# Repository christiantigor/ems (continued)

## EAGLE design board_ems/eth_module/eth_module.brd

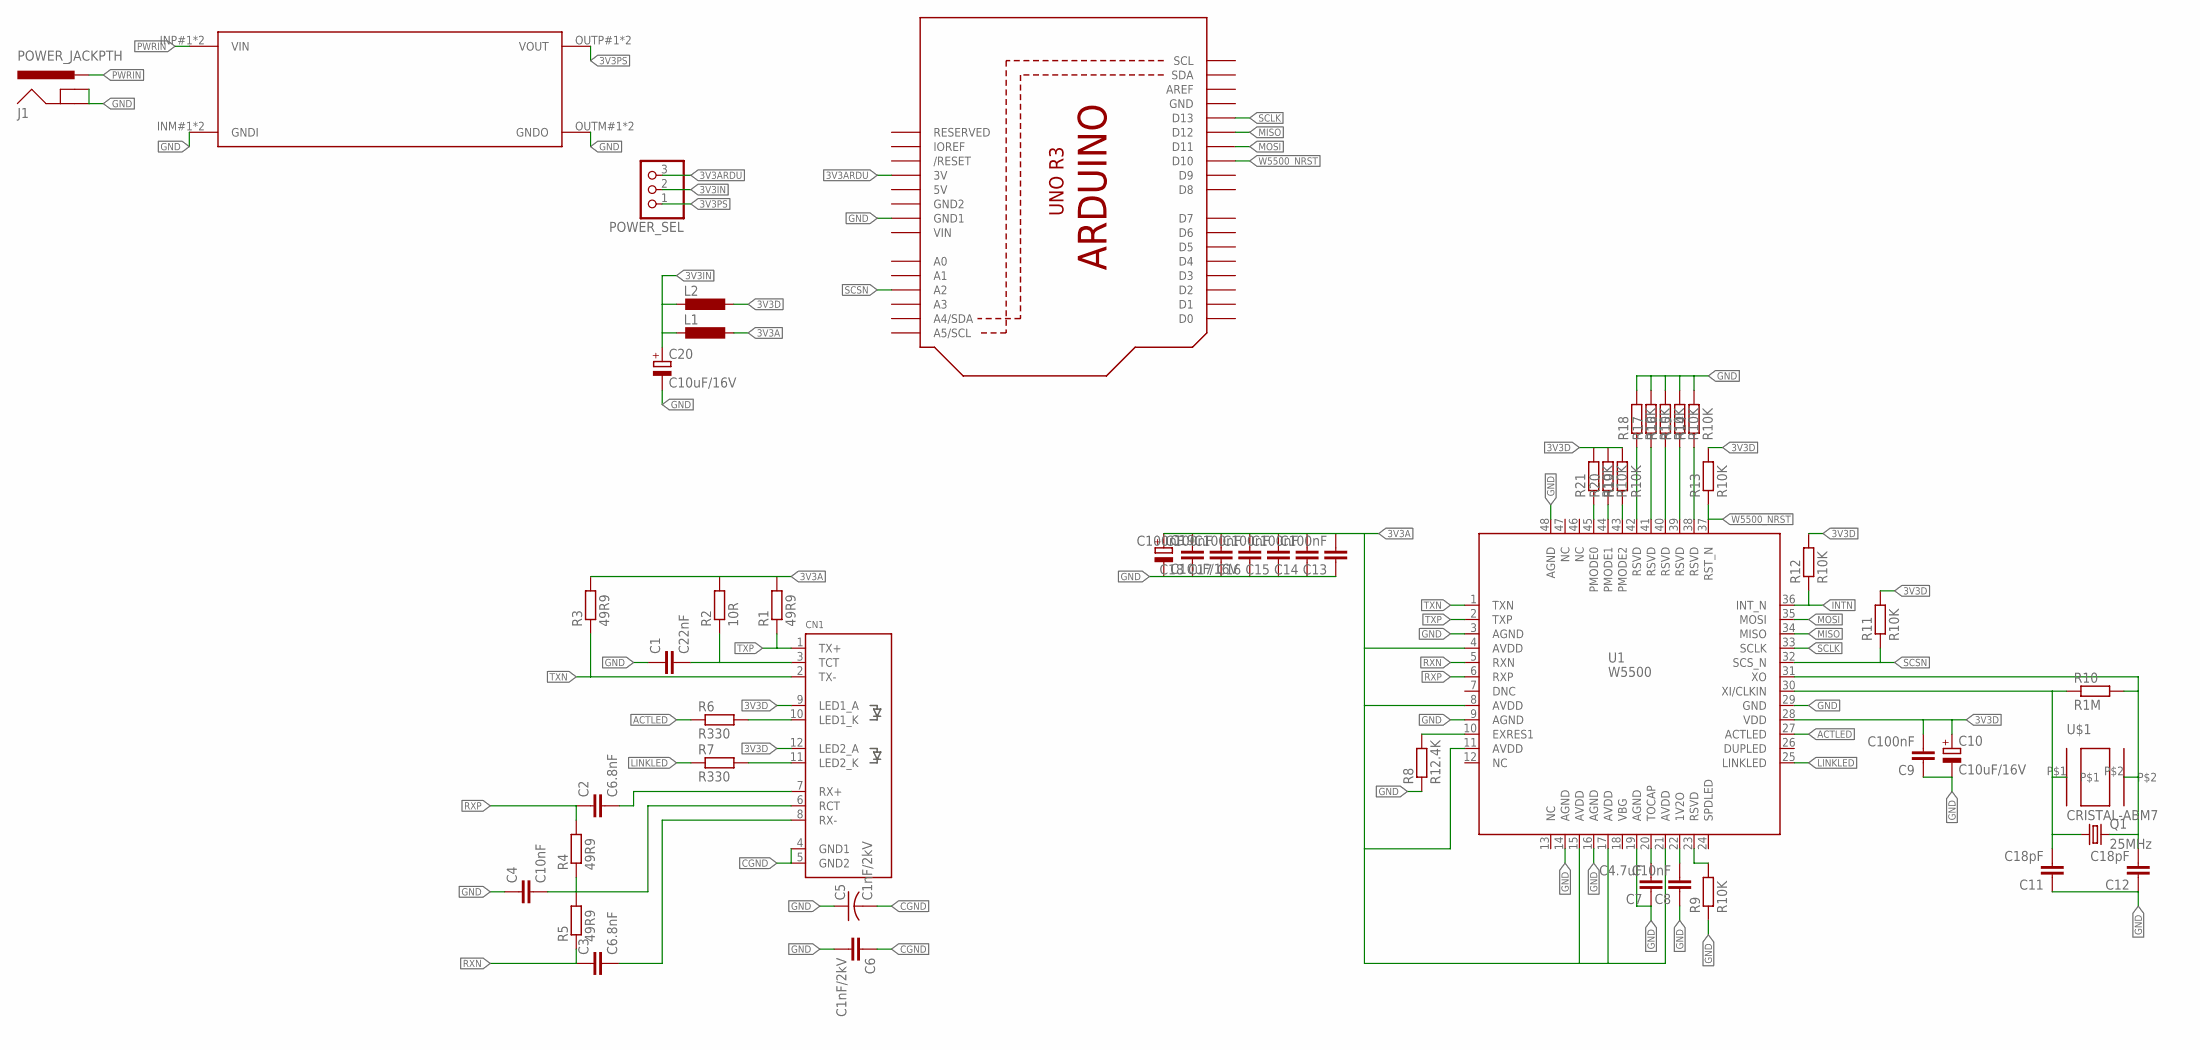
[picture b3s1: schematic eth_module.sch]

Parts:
C1: C22nF; C0603
C2, C3: C6.8nF; C0603
C4, C8: C10nF; C0603
C5: C1nF/2kV; C025-025X050
C6: C1nF/2kV; C0603
C7: C4.7uF; C0603
C9, C13, C14, C15, C16, C17, C18: C100nF; C0603
C10, C19, C20: C10uF/16V; 153CLV-0605
C11, C12: C18pF; C0603
CN1: RJ45J0026D21BNL; RJ45_PULSEJACK
J1: POWER_JACKPTH; POWER_JACK_PTH
L1, L2: L-EUL2012C; L2012C
POWER_SEL: PINHD-1X3; 1X03
Q1: 25MHz; HC49/S
R1, R3, R4, R5: 49R9; R0603
R2: 10R; R0603
R6, R7: R330; R0603
R8: R12.4K; R0805
R9, R11, R12, R13, R14, R15, R16, R17, R18, R19, R20, R21: R10K; R0603
R10: R1M; R0603
U1: W5500
U2: ARDUINOR3-DIMENSION; ARDUINOR3
U$1: CRISTAL-ABM7
U$2: DCDCMODULE_SMALL; DCDCMODULE-SMALL

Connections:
3V3A: C13.2, C14.2, C15.2, C16.2, C17.2, C18.2, C19.+, L1.1, R1.2, R2.2, R3.2, U1.4 (AVDD), U1.8 (AVDD), U1.11 (AVDD), U1.15 (AVDD), U1.17 (AVDD), U1.21 (AVDD)
3V3ARDU: POWER_SEL.3, U2.3V
3V3D: C9.2, C10.+, CN1.9 (LED1_A), CN1.12 (LED2_A), L2.1, R11.2, R12.2, R13.2, R19.2, R20.2, R21.2, U1.28 (VDD)
3V3IN: C20.+, L1.2, L2.2, POWER_SEL.2
3V3PS: POWER_SEL.1, U$2.OUTP#1 (VOUT), U$2.OUTP#2 (VOUT)
5VPS: U2.5V
ACTLED: R6.1, U1.27 (ACTLED)
CGND: C5.2, C6.1, CN1.4 (GND1), CN1.5 (GND2)
GND: C1.1, C4.1, C5.1, C6.2, C7.1, C8.1, C9.1, C10.-, C11.1, C12.1, C13.1, C14.1, C15.1, C16.1, C17.1, C18.1, C19.-, C20.-, J1.GND, J1.GNDBREAK, R8.1, R9.1, R14.2, R15.2, R16.2, R17.2, R18.2, U1.3 (AGND), U1.9 (AGND), U1.14 (AGND), U1.16 (AGND), U1.19 (AGND), U1.29 (GND), U1.48 (AGND), U2.GND, U2.GND1, U$2.INM#1 (GNDI), U$2.INM#2 (GNDI), U$2.OUTM#1 (GNDO), U$2.OUTM#2 (GNDO)
GND2: U2.GND2
INTN: R12.1, U1.36 (INT_N)
LINKLED: R7.1, U1.25 (LINKLED)
MISO: U1.34 (MISO), U2.D12
MOSI: U1.35 (MOSI), U2.D11
unnamed: CN1.10 (LED1_K), R6.2
unnamed: C1.2, CN1.3 (TCT), R2.1
unnamed: CN1.11 (LED2_K), R7.2
unnamed: C2.2, CN1.7 (RX+)
unnamed: C7.2, U1.20 (TOCAP)
unnamed: C4.2, CN1.6 (RCT), R4.1, R5.2
unnamed: R9.2, U1.23 (RSVD)
unnamed: C3.2, CN1.8 (RX-)
unnamed: R8.2, U1.10 (EXRES1)
unnamed: C11.2, Q1.1, R10.1, U1.30 (XI/CLKIN), U$1.P$1
unnamed: C8.2, U1.22 (1V2O)
unnamed: C12.2, Q1.2, R10.2, U1.31 (XO), U$1.P$2
unnamed: R14.1, U1.38 (RSVD)
unnamed: R15.1, U1.39 (RSVD)
unnamed: R16.1, U1.40 (RSVD)
unnamed: R17.1, U1.41 (RSVD)
unnamed: R18.1, U1.42 (RSVD)
unnamed: R21.1, U1.45 (PMODE0)
unnamed: R20.1, U1.44 (PMODE1)
unnamed: R19.1, U1.43 (PMODE2)
PWRIN: J1.PWR, U$2.INP#1 (VIN), U$2.INP#2 (VIN)
RXN: C3.1, R5.1, U1.5 (RXN)
RXP: C2.1, R4.2, U1.6 (RXP)
SCLK: U1.33 (SCLK), U2.D13
SCSN: R11.1, U1.32 (SCS_N), U2.A2
TXN: CN1.2 (TX-), R3.1, U1.1 (TXN)
TXP: CN1.1 (TX+), R1.1, U1.2 (TXP)
VIN: U2.VIN
W5500_NRST: R13.1, U1.37 (RST_N), U2.D10

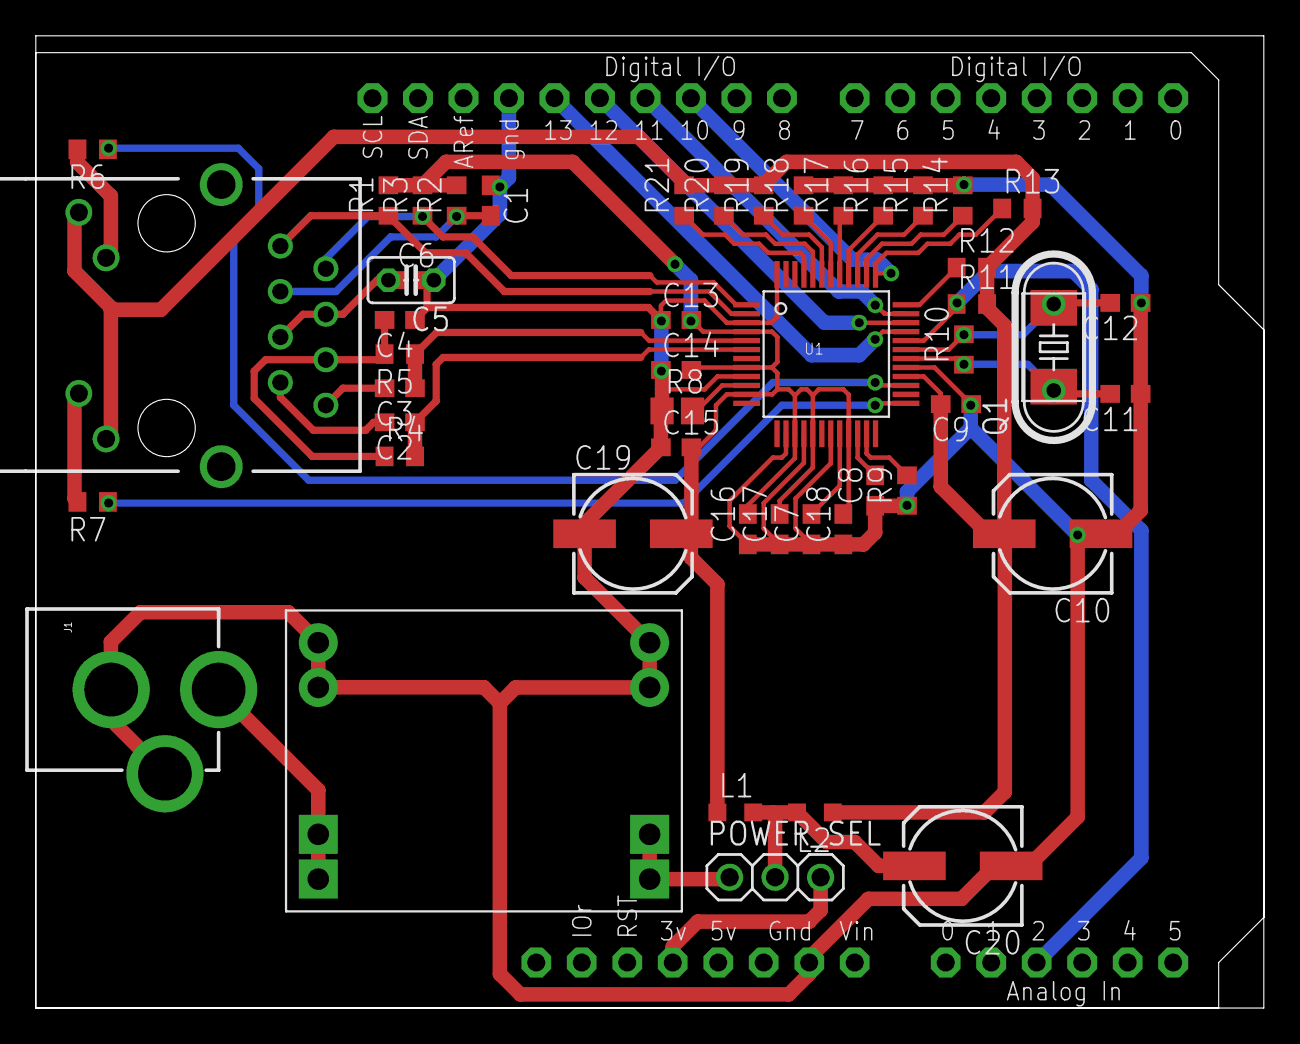
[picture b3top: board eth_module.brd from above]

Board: 2 copper layers, 68.6 x 54.3 mm, 51 parts (0 on the bottom side), 40 nets.

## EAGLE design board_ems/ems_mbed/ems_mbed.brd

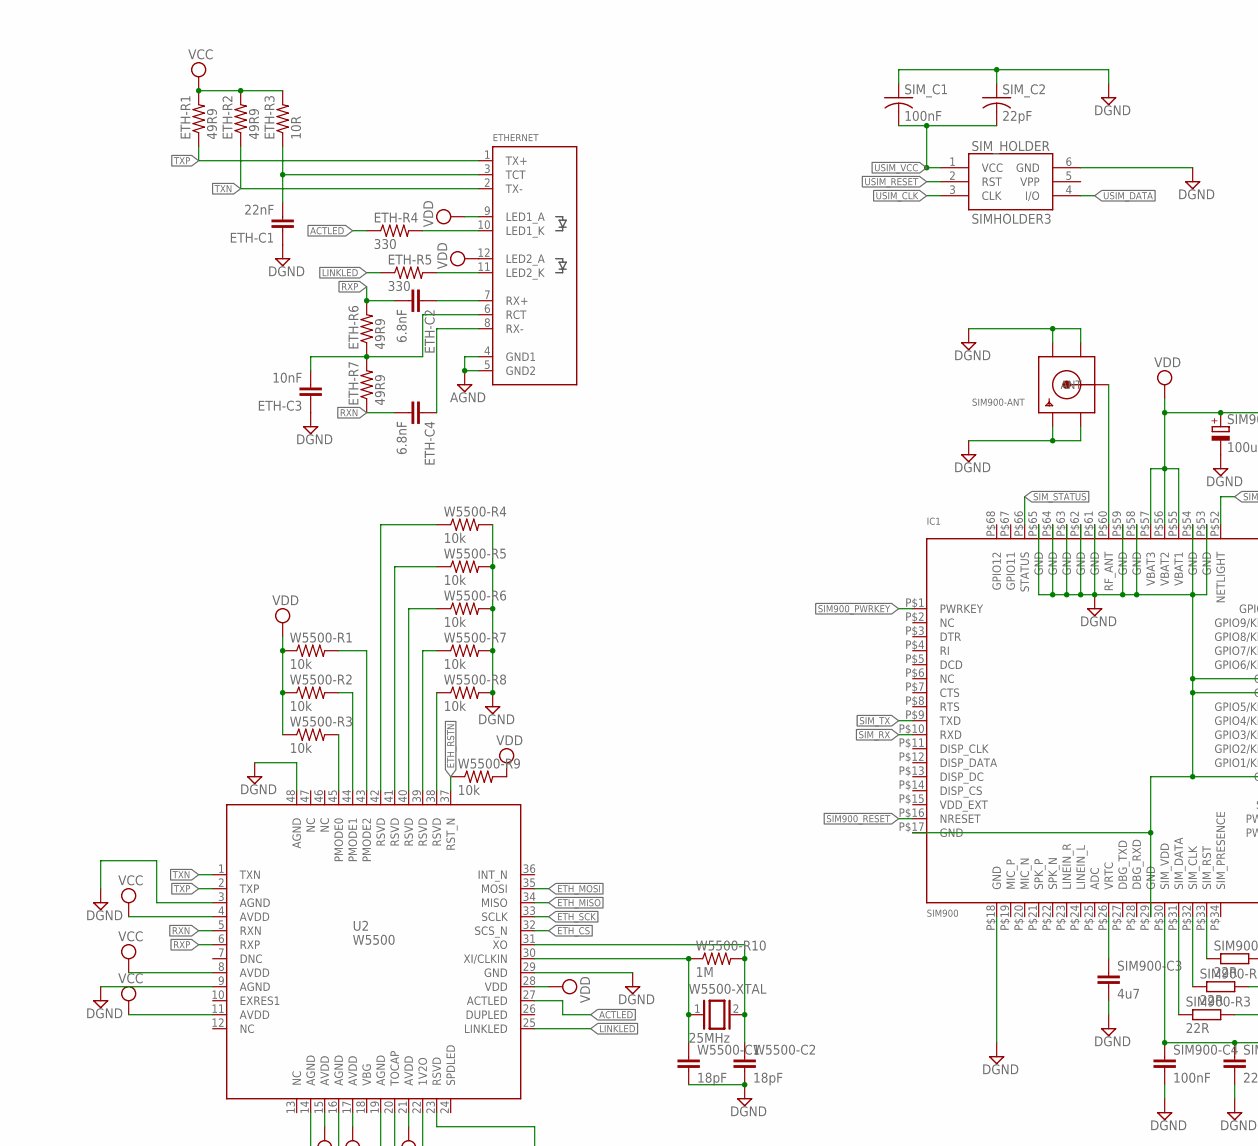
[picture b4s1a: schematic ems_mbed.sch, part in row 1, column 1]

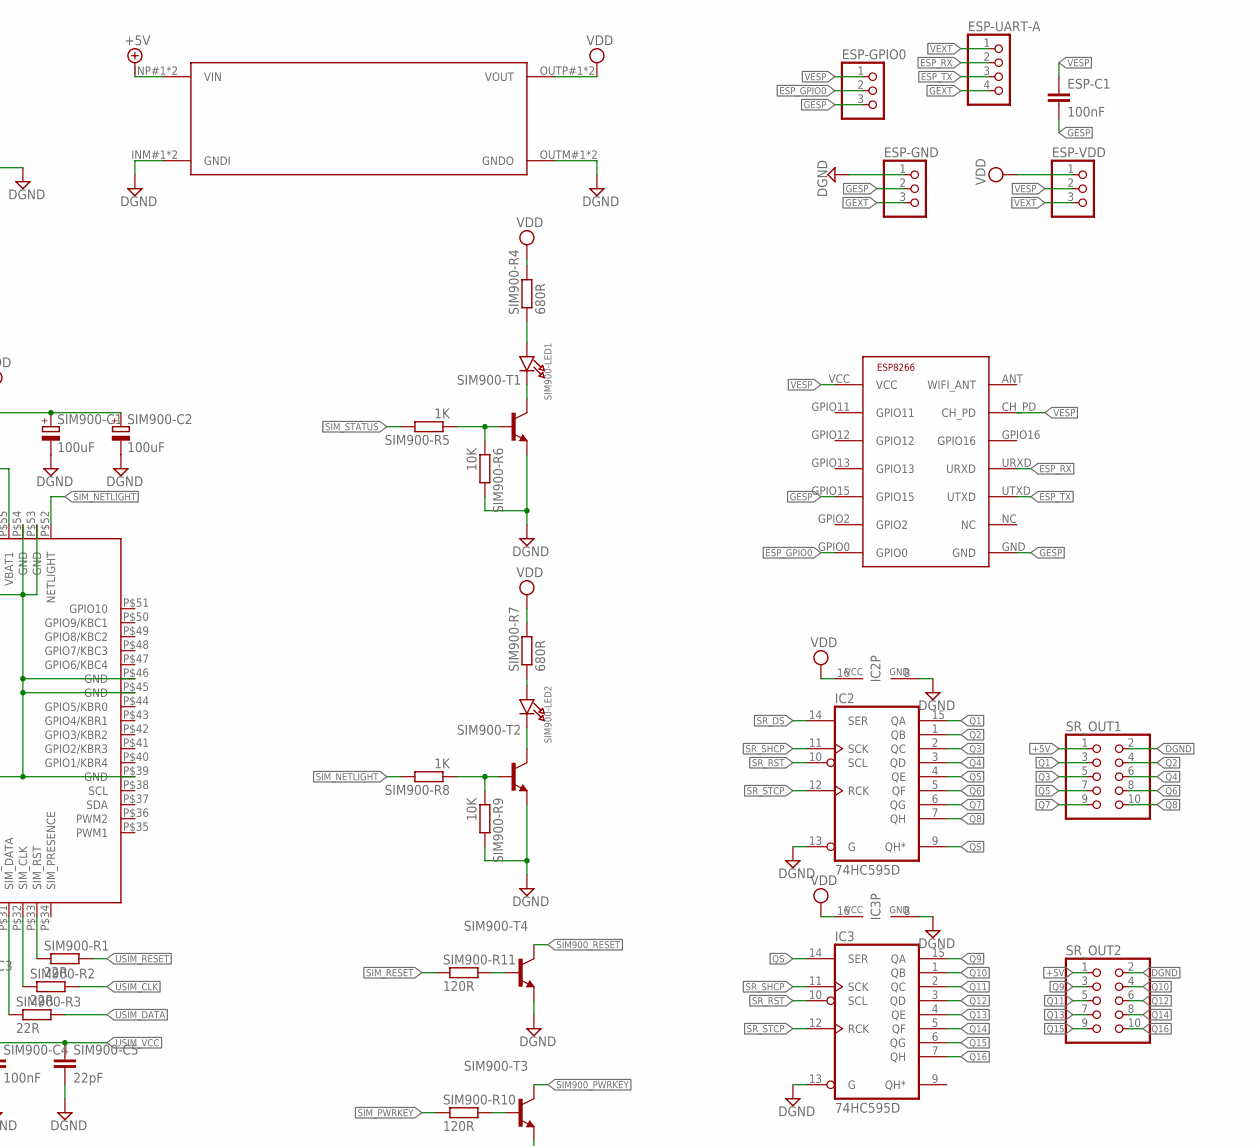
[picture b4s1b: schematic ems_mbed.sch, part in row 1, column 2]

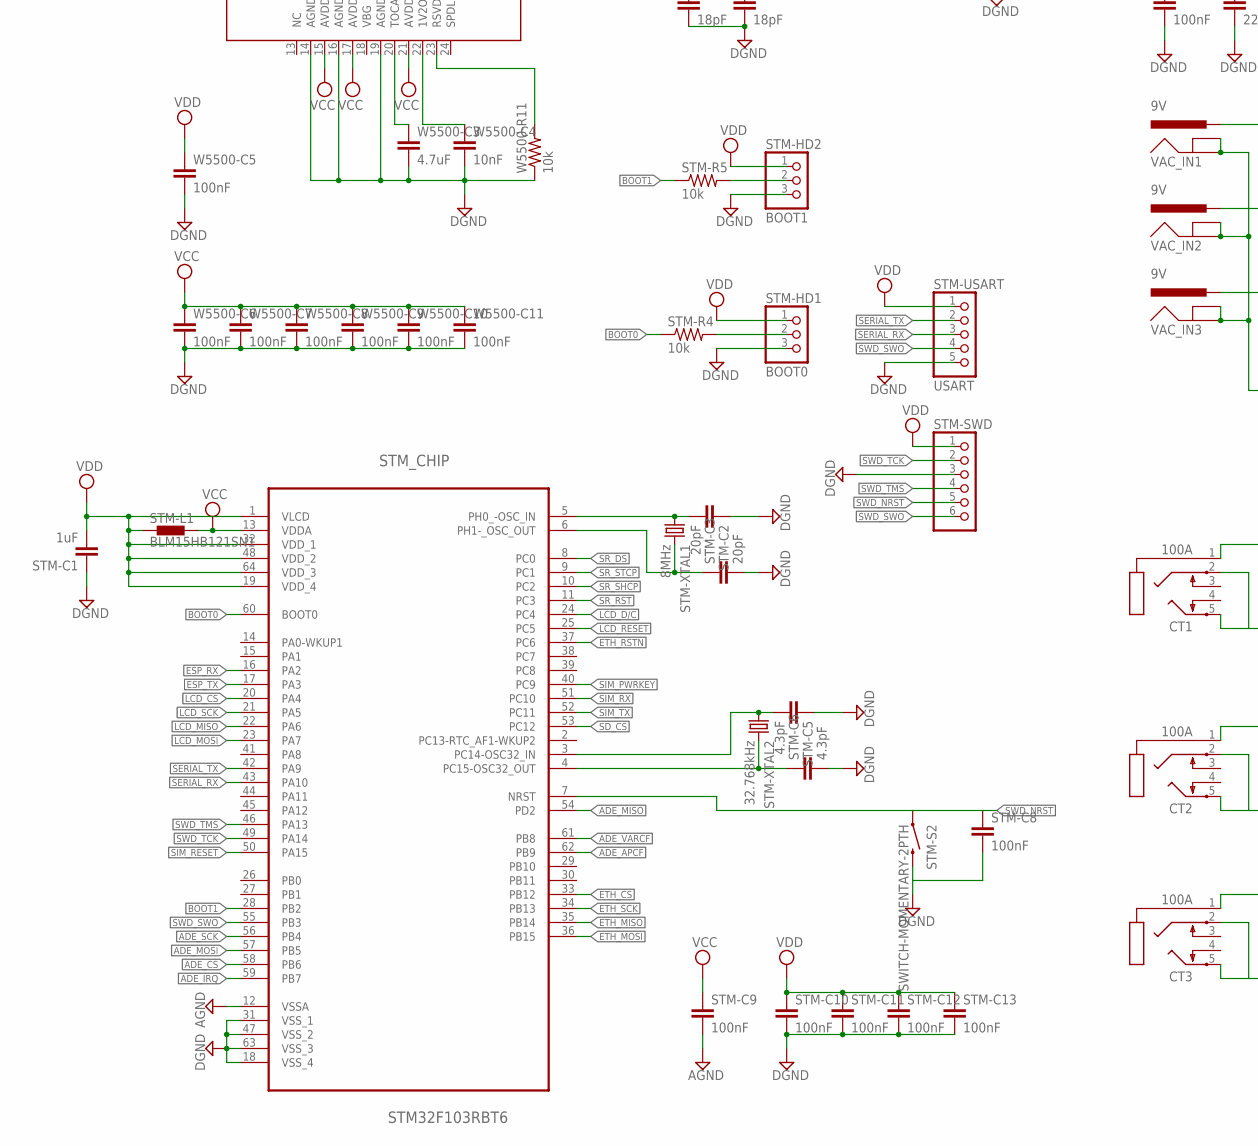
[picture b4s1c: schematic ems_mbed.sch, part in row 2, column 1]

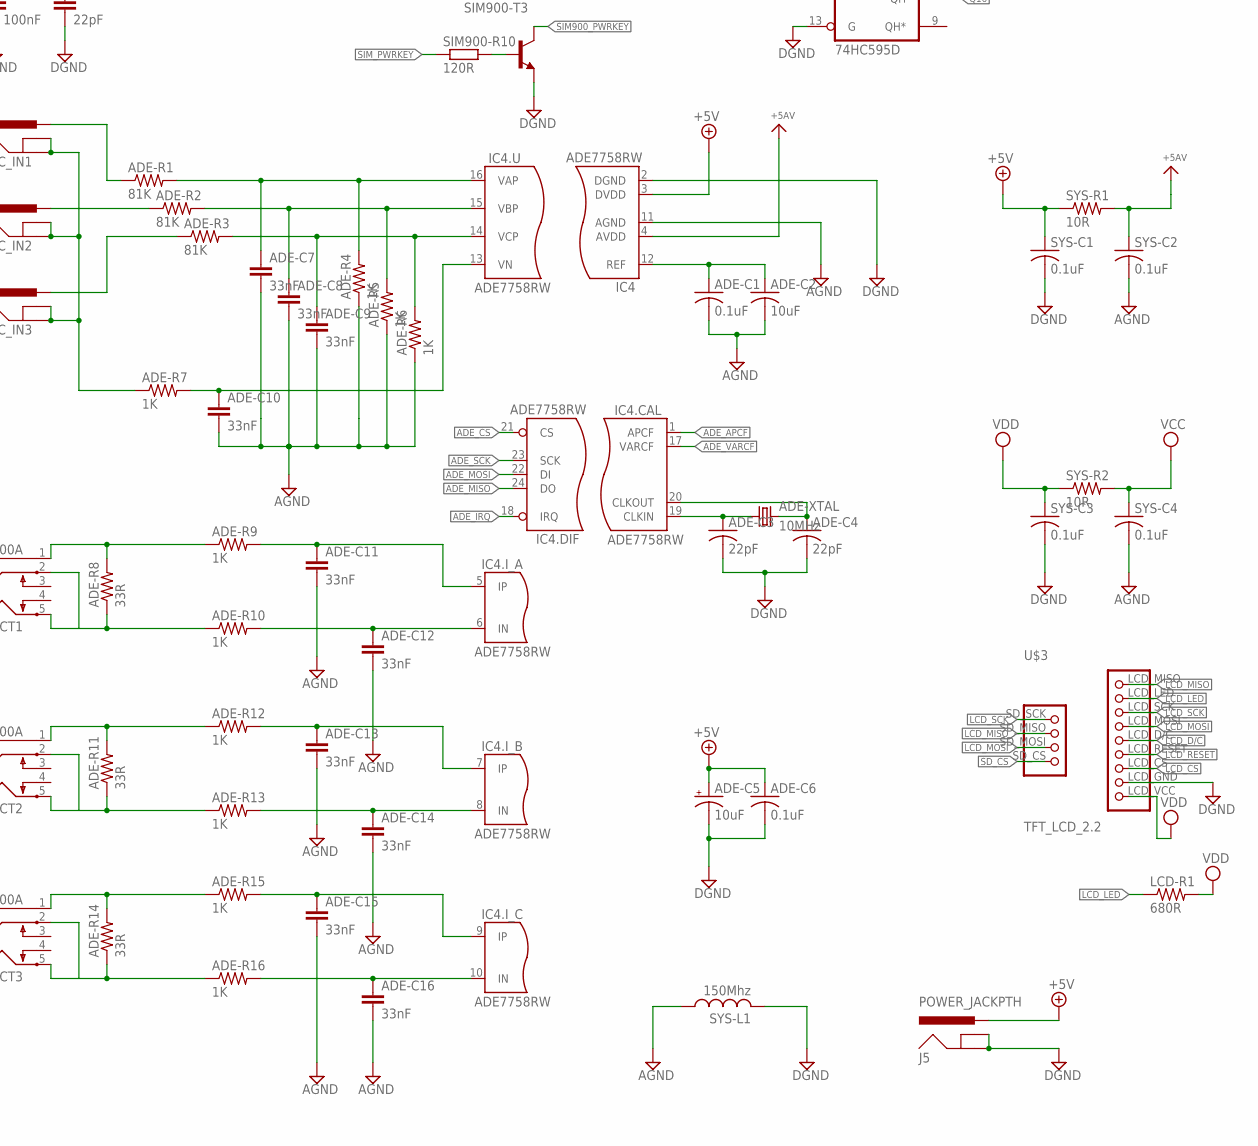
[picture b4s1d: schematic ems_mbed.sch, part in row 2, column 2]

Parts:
ADE-C1, ADE-C6: 0.1uF; C0603@1
ADE-C2: 10uF; C0805K
ADE-C3: 22pF; C0603@1
ADE-C4: 22pF; C0603
ADE-C5: 10uF; 153CLV-0605
ADE-C7, ADE-C8, ADE-C9, ADE-C10, ADE-C11, ADE-C12, ADE-C13, ADE-C14, ADE-C15, ADE-C16: 33nF; 0603-CAP
ADE-R1, ADE-R2, ADE-R3: 81K; 0603-RES
ADE-R4, ADE-R5, ADE-R6, ADE-R7, ADE-R9, ADE-R10, ADE-R12, ADE-R13, ADE-R15, ADE-R16: 1K; 0603-RES
ADE-R8, ADE-R11, ADE-R14: 33R; 0603-RES
ADE-XTAL: 10MHz; HC49US
CT1, CT2, CT3: 100A; STX3100
DCDC-3.5V: DCDCMODULE_SMALL; DCDCMODULE-SMALL
ESP8266: ESP-07
ESP-C1: 100nF; C0603@1
ESP-GND: PINHD-1X3; 1X03
ESP-GPIO0: PINHD-1X3; 1X03
ESP-UART-A: PINHD-1X4; 1X04
ESP-VDD: PINHD-1X3; 1X03
ETH-C1: 22nF; C0603@1
ETH-C2, ETH-C4: 6.8nF; C0603@1
ETH-C3: 10nF; C0603@1
ETH-R1, ETH-R2, ETH-R6, ETH-R7: 49R9; R0603
ETH-R3: 10R; R0603
ETH-R4, ETH-R5: 330; R0603
ETHERNET: RJ45J0026D21BNL; RJ45_PULSEJACK
IC1: SIM900; SIM900_SMT
IC2, IC3: 74HC595D; SO16
IC4: ADE7758RW; SOIC24
J5: POWER_JACKPTH; POWER_JACK_PTH
LCD-R1: 680R; 0603-RES
SIM900-ANT: SMACONNECTOR; SMA90_DIP
SIM900-C1, SIM900-C2: 100uF; 153CLV-0605
SIM900-C3: 4u7; C0603@1
SIM900-C4: 100nF; C0603@1
SIM900-C5: 22pF; C0603@1
SIM900-LED1, SIM900-LED2: LED0805_NOOUTLINE; CHIPLED_0805_NOOUTLINE
SIM900-R1, SIM900-R2, SIM900-R3: 22R; R0603
SIM900-R4, SIM900-R7: 680R; R0603
SIM900-R5, SIM900-R8: 1K; R0603
SIM900-R6, SIM900-R9: 10K; R0603
SIM900-R10, SIM900-R11: 120R; R0603
SIM900-T1, SIM900-T2, SIM900-T3, SIM900-T4: MMBT2222ALT1-NPN-SOT23-BEC; SOT23-BEC
SIM_C1: 100nF; C0603K
SIM_C2: 22pF; C0603K
SIM_HOLDER: SIMHOLDER3
SR_OUT1, SR_OUT2: PINHD-2X5/90; 2X05/90
STM-C1: 1uF; C0603@1
STM-C2, STM-C3: 20pF; C0603@1
STM-C5, STM-C6: 4.3pF; C0603@1
STM-C8, STM-C9, STM-C10, STM-C11, STM-C12, STM-C13: 100nF; C0603@1
STM-HD1: BOOT0; 1X03
STM-HD2: BOOT1; 1X03
STM-L1: BLM15HB121SN1; 0402
STM-R4, STM-R5: 10k; R0603
STM-S2: SWITCH-MOMENTARY-2PTH; TACTILE-PTH
STM-SWD: PINHD-1X6; 1X06
STM-USART: USART; PINHD5
STM-XTAL1: 8MHz; TC26H
STM-XTAL2: 32.768kHz; TC26H
STM_CHIP: STM32F103RBT6; QFP50P1200X1200X160-64N
SYS-C1, SYS-C2, SYS-C3, SYS-C4: 0.1uF; C0603@1
SYS-L1: 150Mhz; POWER-CHOKE_WE-TPC
SYS-R1, SYS-R2: 10R; 0603-RES
U2: W5500
U$3: TFT_LCD_2.2
VAC_IN1, VAC_IN2, VAC_IN3: 9V; POWER_JACK_PTH
W5500-C1, W5500-C2: 18pF; C0603@1
W5500-C3: 4.7uF; C0603@1
W5500-C4: 10nF; C0603@1
W5500-C5, W5500-C6, W5500-C7, W5500-C8, W5500-C9, W5500-C10, W5500-C11: 100nF; C0603@1
W5500-R1, W5500-R2, W5500-R3, W5500-R4, W5500-R5, W5500-R6, W5500-R7, W5500-R8, W5500-R9, W5500-R11: 10k; R0603
W5500-R10: 1M; R0603
W5500-XTAL: 25MHz; QS

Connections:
+5V: ADE-C5.+, ADE-C6.1, DCDC-3.5V.INP#1 (VIN), DCDC-3.5V.INP#2 (VIN), IC4.3 (DVDD), J5.PWR, SR_OUT1.1, SR_OUT2.1, SYS-C1.1, SYS-R1.1
ACTLED: ETH-R4.1, U2.27 (ACTLED)
ADE_APCF: IC4.1 (APCF), STM_CHIP.62 (PB9)
ADE_CS: IC4.21 (CS), STM_CHIP.58 (PB6)
ADE_IRQ: IC4.18 (IRQ), STM_CHIP.59 (PB7)
ADE_MISO: IC4.24 (DO), STM_CHIP.54 (PD2)
ADE_MOSI: IC4.22 (DI), STM_CHIP.57 (PB5)
ADE_SCK: IC4.23 (SCK), STM_CHIP.56 (PB4)
ADE_VARCF: IC4.17 (VARCF), STM_CHIP.61 (PB8)
AGND: ADE-C1.2, ADE-C2.2, ADE-C7.2, ADE-C8.2, ADE-C9.2, ADE-C10.2, ADE-C11.2, ADE-C12.2, ADE-C13.2, ADE-C14.2, ADE-C15.2, ADE-C16.2, ADE-R4.1, ADE-R5.1, ADE-R6.1, ETHERNET.4 (GND1), ETHERNET.5 (GND2), IC4.11 (AGND), STM-C9.2, STM_CHIP.12 (VSSA), SYS-C2.2, SYS-C4.2, SYS-L1.1
AVDD: IC4.4 (AVDD), SYS-C2.1, SYS-R1.2
BOOT0: STM-R4.1, STM_CHIP.60 (BOOT0)
BOOT1: STM-R5.1, STM_CHIP.28 (PB2)
DGND: ADE-C3.2, ADE-C4.2, ADE-C5.-, ADE-C6.2, DCDC-3.5V.INM#1 (GNDI), DCDC-3.5V.INM#2 (GNDI), DCDC-3.5V.OUTM#1 (GNDO), DCDC-3.5V.OUTM#2 (GNDO), ESP-GND.1, ETH-C1.1, ETH-C3.1, IC1.P$17 (GND), IC1.P$18 (GND), IC1.P$29 (GND), IC1.P$39 (GND), IC1.P$45 (GND), IC1.P$46 (GND), IC1.P$53 (GND), IC1.P$54 (GND), IC1.P$58 (GND), IC1.P$59 (GND), IC1.P$61 (GND), IC1.P$62 (GND), IC1.P$63 (GND), IC1.P$64 (GND), IC1.P$65 (GND), IC2.8 (GND), IC2.13 (G), IC3.8 (GND), IC3.13 (G), IC4.2 (DGND), J5.GND, J5.GNDBREAK, SIM900-ANT.GND1, SIM900-ANT.GND2, SIM900-ANT.GND3, SIM900-ANT.GND4, SIM900-C1.-, SIM900-C2.-, SIM900-C3.2, SIM900-C4.2, SIM900-C5.2, SIM900-R6.2, SIM900-R9.2, SIM900-T1.E, SIM900-T2.E, SIM900-T3.E, SIM900-T4.E, SIM_C1.1, SIM_C2.1, SIM_HOLDER.6 (GND), SR_OUT1.2, SR_OUT2.2, STM-C1.1, STM-C2.1, STM-C3.2, STM-C5.1, STM-C6.2, STM-C8.2, STM-C10.2, STM-C11.2, STM-C12.2, STM-C13.2, STM-HD1.3, STM-HD2.3, STM-S2.3 (2), STM-SWD.3, STM-USART.5, STM_CHIP.18 (VSS_4), STM_CHIP.31 (VSS_1), STM_CHIP.47 (VSS_2), STM_CHIP.63 (VSS_3), SYS-C1.2, SYS-C3.2, SYS-L1.2, U2.3 (AGND), U2.9 (AGND), U2.14 (AGND), U2.16 (AGND), U2.19 (AGND), U2.29 (GND), U2.48 (AGND), U$3.LCD_GND, W5500-C1.2, W5500-C2.2, W5500-C3.2, W5500-C4.2, W5500-C5.2, W5500-C6.2, W5500-C7.2, W5500-C8.2, W5500-C9.2, W5500-C10.2, W5500-C11.2, W5500-R4.2, W5500-R5.2, W5500-R6.2, W5500-R7.2, W5500-R8.2, W5500-R11.1
ESP_GPIO0: ESP8266.GPIO0, ESP-GPIO0.2
ESP_RX: ESP8266.URXD, ESP-UART-A.2, STM_CHIP.16 (PA2)
ESP_TX: ESP8266.UTXD, ESP-UART-A.3, STM_CHIP.17 (PA3)
ETH_CS: STM_CHIP.33 (PB12), U2.32 (SCS_N)
ETH_MISO: STM_CHIP.35 (PB14), U2.34 (MISO)
ETH_MOSI: STM_CHIP.36 (PB15), U2.35 (MOSI)
ETH_RSTN: STM_CHIP.37 (PC6), U2.37 (RST_N), W5500-R9.1
ETH_SCK: STM_CHIP.34 (PB13), U2.33 (SCLK)
GESP: ESP8266.GND, ESP8266.GPIO15, ESP-C1.2, ESP-GND.2, ESP-GPIO0.3
GEXT: ESP-GND.3, ESP-UART-A.4
GPIO11: IC1.P$67 (GPIO11)
GPIO12: IC1.P$68 (GPIO12)
IBN: ADE-R11.1, ADE-R13.1, CT2.2, CT2.5
ICN: ADE-R14.1, ADE-R16.1, CT3.2, CT3.5
LCD_CS: STM_CHIP.20 (PA4), U$3.LCD_CS
LCD_D/C: STM_CHIP.24 (PC4), U$3.LCD_D/C
LCD_LED: LCD-R1.1, U$3.LCD_LED
LCD_MISO: STM_CHIP.22 (PA6), U$3.LCD_MISO, U$3.SD_MISO
LCD_MOSI: STM_CHIP.23 (PA7), U$3.LCD_MOSI, U$3.SD_MOSI
LCD_RESET: STM_CHIP.25 (PC5), U$3.LCD_RESET
LCD_SCK: STM_CHIP.21 (PA5), U$3.LCD_SCK, U$3.SD_SCK
LINKLED: ETH-R5.1, U2.25 (LINKLED)
unnamed: STM-C5.2, STM-XTAL2.1, STM_CHIP.3 (PC14-OSC32_IN)
unnamed: STM-C6.1, STM-XTAL2.2, STM_CHIP.4 (PC15-OSC32_OUT)
unnamed: IC1.P$31 (SIM_DATA), SIM900-R3.1
unnamed: STM-HD1.2, STM-R4.2
unnamed: STM-C2.2, STM-XTAL1.1, STM_CHIP.5 (PH0_-OSC_IN)
unnamed: STM-C3.1, STM-XTAL1.2, STM_CHIP.6 (PH1-_OSC_OUT)
unnamed: IC1.P$32 (SIM_CLK), SIM900-R2.1
unnamed: ADE-C9.1, ADE-R3.2, ADE-R6.2, IC4.14 (VCP)
unnamed: ETH-R4.2, ETHERNET.10 (LED1_K)
unnamed: ETH-R5.2, ETHERNET.11 (LED2_K)
unnamed: IC1.P$33 (SIM_RST), SIM900-R1.1
unnamed: IC1.P$26 (VRTC), SIM900-C3.1
unnamed: IC1.P$60 (RF_ANT), SIM900-ANT.ANTENNA (ANT)
unnamed: SIM900-LED1.A, SIM900-R4.1
unnamed: SIM900-LED1.C, SIM900-T1.C
unnamed: SIM900-R5.1, SIM900-R6.1, SIM900-T1.B
unnamed: SIM900-LED2.A, SIM900-R7.1
unnamed: SIM900-LED2.C, SIM900-T2.C
unnamed: SIM900-R8.1, SIM900-R9.1, SIM900-T2.B
unnamed: ETH-C2.1, ETHERNET.7 (RX+)
unnamed: ETH-C1.2, ETH-R3.1, ETHERNET.3 (TCT)
unnamed: ADE-C15.1, ADE-R15.2, IC4.9 (IP)
unnamed: ADE-R11.2, ADE-R12.1, CT2.1
unnamed: ETH-C4.1, ETHERNET.8 (RX-)
unnamed: ADE-C11.1, ADE-R9.2, IC4.5 (IP)
unnamed: ADE-C12.1, ADE-R10.2, IC4.6 (IN)
unnamed: ETH-C3.2, ETH-R6.1, ETH-R7.2, ETHERNET.6 (RCT)
unnamed: ADE-C14.1, ADE-R13.2, IC4.8 (IN)
unnamed: ADE-C13.1, ADE-R12.2, IC4.7 (IP)
unnamed: ADE-C1.1, ADE-C2.1, IC4.12 (REF)
unnamed: ADE-C3.1, ADE-XTAL.1, IC4.19 (CLKIN)
unnamed: ADE-C4.1, ADE-XTAL.2, IC4.20 (CLKOUT)
unnamed: ADE-C10.1, ADE-R7.2, IC4.13 (VN)
unnamed: ADE-R2.1, VAC_IN2.PWR
unnamed: ADE-C8.1, ADE-R2.2, ADE-R5.2, IC4.15 (VBP)
unnamed: U2.20 (TOCAP), W5500-C3.1
unnamed: ADE-R8.2, ADE-R9.1, CT1.1
unnamed: ADE-C16.1, ADE-R16.2, IC4.10 (IN)
unnamed: U2.22 (1V2O), W5500-C4.1
unnamed: U2.23 (RSVD), W5500-R11.2
unnamed: SIM900-R10.2, SIM900-T3.B
unnamed: SIM900-R11.2, SIM900-T4.B
unnamed: STM-HD2.2, STM-R5.2
unnamed: ADE-R8.1, ADE-R10.1, CT1.2, CT1.5
unnamed: ADE-R14.2, ADE-R15.1, CT3.1
unnamed: U2.30 (XI/CLKIN), W5500-C1.1, W5500-R10.1, W5500-XTAL.1
unnamed: U2.31 (XO), W5500-C2.1, W5500-R10.2, W5500-XTAL.2
unnamed: ADE-C7.1, ADE-R1.2, ADE-R4.2, IC4.16 (VAP)
unnamed: ADE-R1.1, VAC_IN1.PWR
unnamed: ADE-R7.1, VAC_IN1.GND, VAC_IN1.GNDBREAK, VAC_IN2.GND, VAC_IN2.GNDBREAK, VAC_IN3.GND, VAC_IN3.GNDBREAK
unnamed: U2.38 (RSVD), W5500-R8.1
unnamed: U2.39 (RSVD), W5500-R7.1
unnamed: U2.40 (RSVD), W5500-R6.1
unnamed: U2.41 (RSVD), W5500-R5.1
unnamed: U2.42 (RSVD), W5500-R4.1
unnamed: U2.43 (PMODE2), W5500-R1.2
unnamed: U2.44 (PMODE1), W5500-R2.2
unnamed: U2.45 (PMODE0), W5500-R3.2
unnamed: ADE-R3.1, VAC_IN3.PWR
Q1: IC2.15 (QA), SR_OUT1.3
Q2: IC2.1 (QB), SR_OUT1.4
Q3: IC2.2 (QC), SR_OUT1.5
Q4: IC2.3 (QD), SR_OUT1.6
Q5: IC2.4 (QE), SR_OUT1.7
Q6: IC2.5 (QF), SR_OUT1.8
Q7: IC2.6 (QG), SR_OUT1.9
Q8: IC2.7 (QH), SR_OUT1.10
Q9: IC3.15 (QA), SR_OUT2.3
Q10: IC3.1 (QB), SR_OUT2.4
Q11: IC3.2 (QC), SR_OUT2.5
Q12: IC3.3 (QD), SR_OUT2.6
Q13: IC3.4 (QE), SR_OUT2.7
Q14: IC3.5 (QF), SR_OUT2.8
Q15: IC3.6 (QG), SR_OUT2.9
Q16: IC3.7 (QH), SR_OUT2.10
QS: IC2.9 (QH*), IC3.14 (SER)
RXN: ETH-C4.2, ETH-R7.1, U2.5 (RXN)
RXP: ETH-C2.2, ETH-R6.2, U2.6 (RXP)
SD_CS: STM_CHIP.53 (PC12), U$3.SD_CS
SERIAL_RX: STM-USART.3, STM_CHIP.43 (PA10)
SERIAL_TX: STM-USART.2, STM_CHIP.42 (PA9)
SIM900_PWRKEY: IC1.P$1 (PWRKEY), SIM900-T3.C
SIM900_RESET: IC1.P$16 (NRESET), SIM900-T4.C
SIM_NETLIGHT: IC1.P$52 (NETLIGHT), SIM900-R8.2
SIM_PWRKEY: SIM900-R10.1, STM_CHIP.40 (PC9)
SIM_RESET: SIM900-R11.1, STM_CHIP.50 (PA15)
SIM_RX: IC1.P$10 (RXD), STM_CHIP.51 (PC10)
SIM_STATUS: IC1.P$66 (STATUS), SIM900-R5.2
SIM_TX: IC1.P$9 (TXD), STM_CHIP.52 (PC11)
SR_DS: IC2.14 (SER), STM_CHIP.8 (PC0)
SR_RST: IC2.10 (SCL), IC3.10 (SCL), STM_CHIP.11 (PC3)
SR_SHCP: IC2.11 (SCK), IC3.11 (SCK), STM_CHIP.10 (PC2)
SR_STCP: IC2.12 (RCK), IC3.12 (RCK), STM_CHIP.9 (PC1)
SWD_NRST: STM-C8.1, STM-S2.1, STM-SWD.5, STM_CHIP.7 (NRST)
SWD_SWO: STM-SWD.6, STM-USART.4, STM_CHIP.55 (PB3)
SWD_TCK: STM-SWD.2, STM_CHIP.49 (PA14)
SWD_TMS: STM-SWD.4, STM_CHIP.46 (PA13)
TXN: ETH-R2.1, ETHERNET.2 (TX-), U2.1 (TXN)
TXP: ETH-R1.1, ETHERNET.1 (TX+), U2.2 (TXP)
USIM_CLK: SIM900-R2.2, SIM_HOLDER.3 (CLK)
USIM_DATA: SIM900-R3.2, SIM_HOLDER.4 (I/O)
USIM_RESET: SIM900-R1.2, SIM_HOLDER.2 (RST)
USIM_VCC: IC1.P$30 (SIM_VDD), SIM900-C4.1, SIM900-C5.1, SIM_C1.2, SIM_C2.2, SIM_HOLDER.1 (VCC)
VCC: ETH-R1.2, ETH-R2.2, ETH-R3.2, STM-C9.1, STM-L1.2, STM_CHIP.13 (VDDA), SYS-C4.1, SYS-R2.2, U2.4 (AVDD), U2.8 (AVDD), U2.11 (AVDD), U2.15 (AVDD), U2.17 (AVDD), U2.21 (AVDD), W5500-C6.1, W5500-C7.1, W5500-C8.1, W5500-C9.1, W5500-C10.1, W5500-C11.1
VDD: DCDC-3.5V.OUTP#1 (VOUT), DCDC-3.5V.OUTP#2 (VOUT), ESP-VDD.1, ETHERNET.9 (LED1_A), ETHERNET.12 (LED2_A), IC1.P$55 (VBAT1), IC1.P$56 (VBAT2), IC1.P$57 (VBAT3), IC2.16 (VCC), IC3.16 (VCC), LCD-R1.2, SIM900-C1.+, SIM900-C2.+, SIM900-R4.2, SIM900-R7.2, STM-C1.2, STM-C10.1, STM-C11.1, STM-C12.1, STM-C13.1, STM-HD1.1, STM-HD2.1, STM-L1.1, STM-SWD.1, STM-USART.1, STM_CHIP.1 (VLCD), STM_CHIP.19 (VDD_4), STM_CHIP.32 (VDD_1), STM_CHIP.48 (VDD_2), STM_CHIP.64 (VDD_3), SYS-C3.1, SYS-R2.1, U2.28 (VDD), U$3.LCD_VCC, W5500-C5.1, W5500-R1.1, W5500-R2.1, W5500-R3.1, W5500-R9.2
VESP: ESP8266.CH_PD, ESP8266.VCC, ESP-C1.1, ESP-GPIO0.1, ESP-VDD.2
VEXT: ESP-UART-A.1, ESP-VDD.3

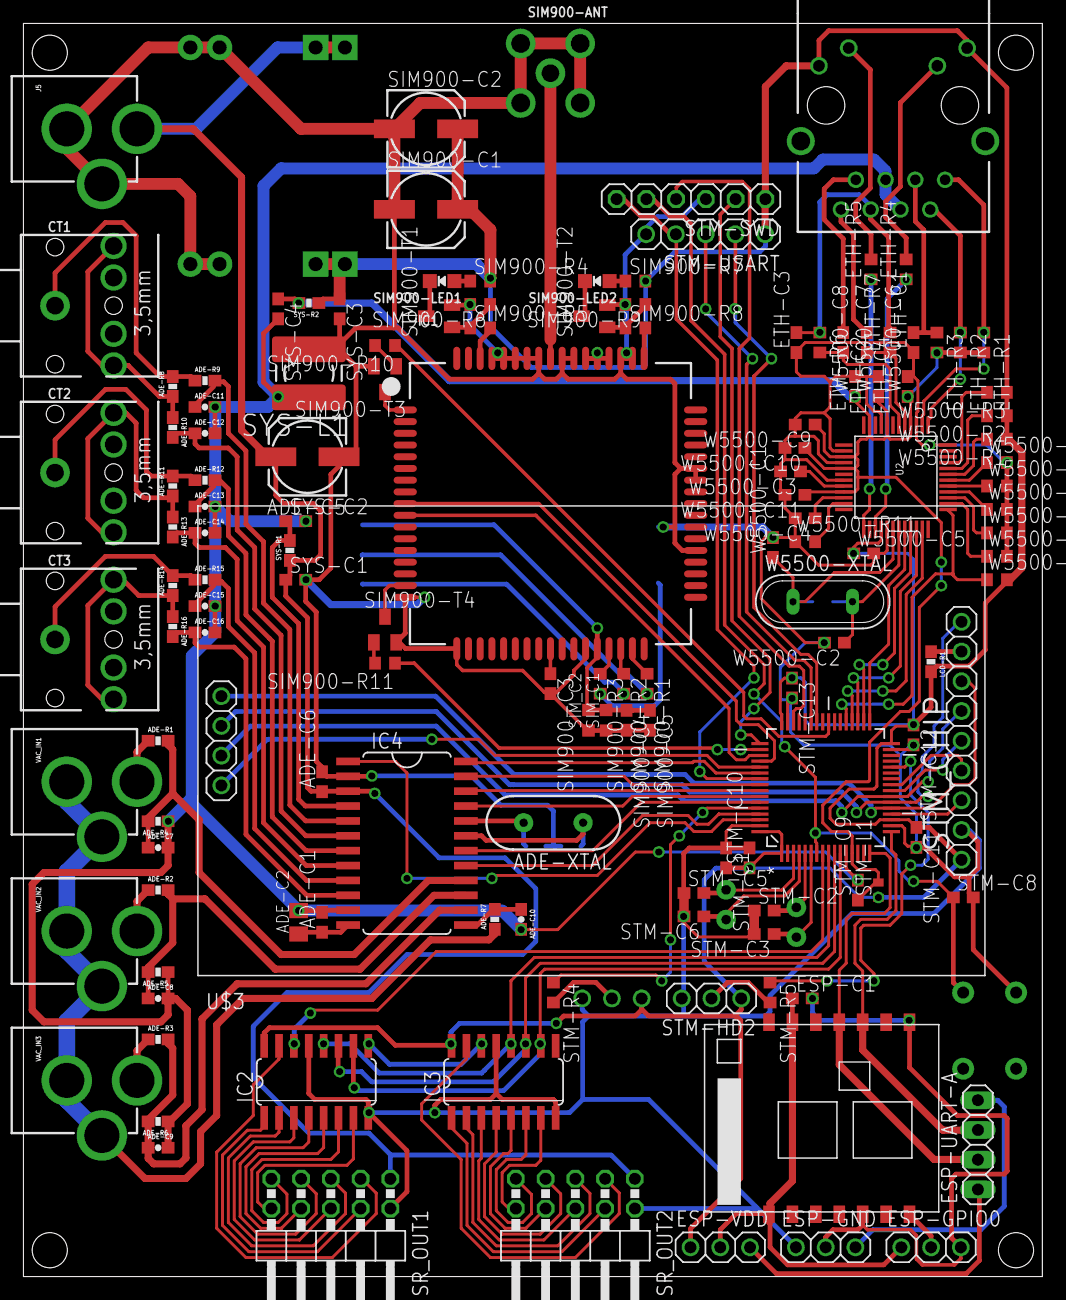
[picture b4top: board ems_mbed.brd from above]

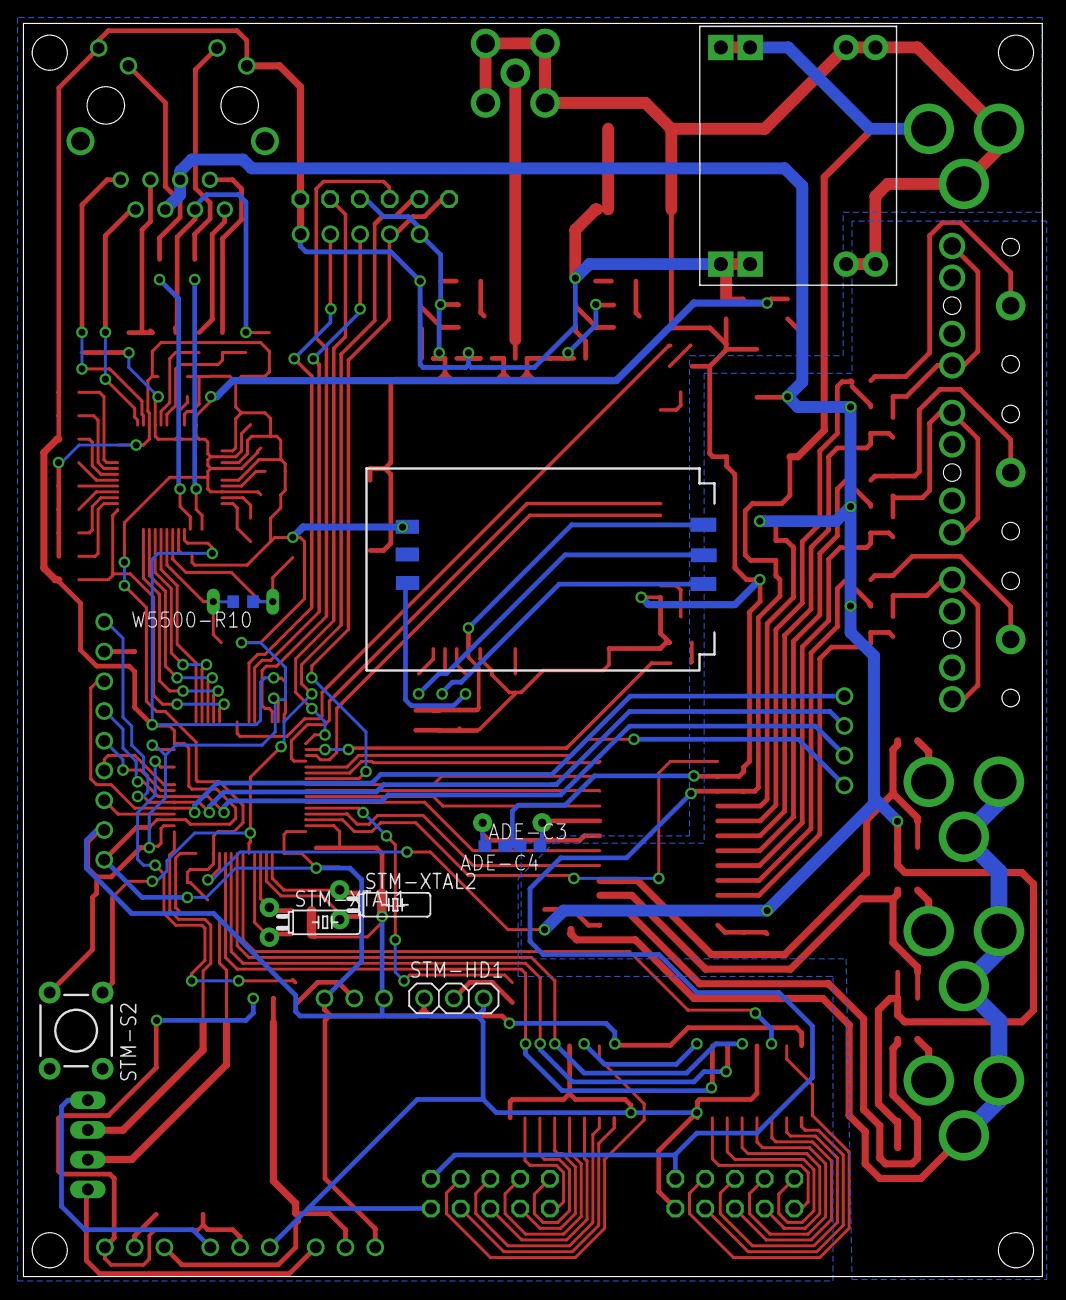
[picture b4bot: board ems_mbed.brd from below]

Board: 2 copper layers, 87.0 x 107.0 mm, 146 parts (9 on the bottom side), 141 nets.

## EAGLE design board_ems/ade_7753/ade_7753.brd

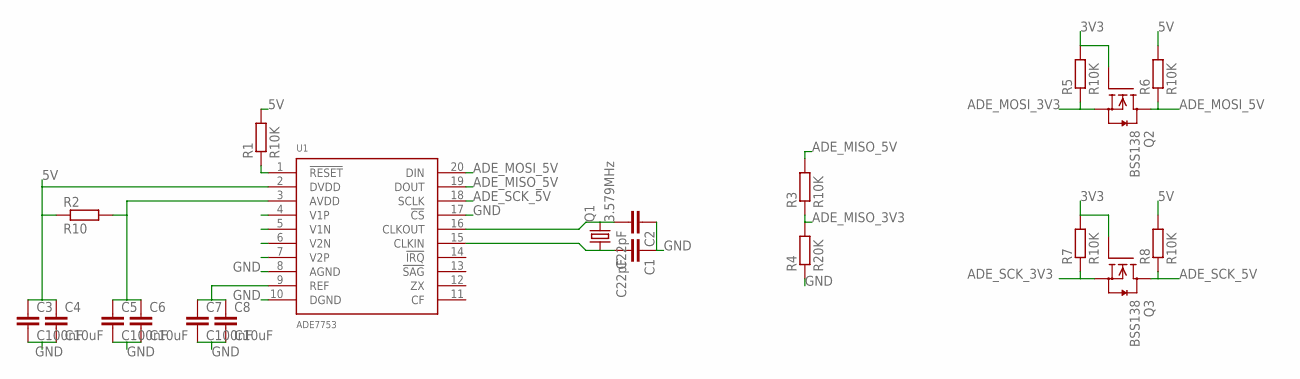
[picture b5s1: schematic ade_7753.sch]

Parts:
C1, C2: C22pF; C0805
C3, C5, C7: C100nF; C0805
C4, C6, C8: C10uF; C0805
Q1: 3.579MHz; HC49/S
Q2, Q3: BSS138; SOT23
R1, R3, R5, R6, R7, R8: R10K; M0805
R2: R10; M0805
R4: R20K; M0805
U1: ADE7753; SSOP-20

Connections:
3V3: Q2.1 (G), Q3.1 (G), R5.2, R7.2
5V: C3.1, C4.1, R1.2, R2.1, R6.2, R8.2, U1.2 (DVDD)
ADE_MISO_3V3: R3.1, R4.2
ADE_MISO_5V: R3.2, U1.19 (DOUT)
ADE_MOSI_3V3: Q2.2 (S), R5.1
ADE_MOSI_5V: Q2.3 (D), R6.1, U1.20 (DIN)
ADE_SCK_3V3: Q3.2 (S), R7.1
ADE_SCK_5V: Q3.3 (D), R8.1, U1.18 (SCLK)
GND: C1.1, C2.1, C3.2, C4.2, C5.2, C6.2, C7.2, C8.2, R4.1, U1.8 (AGND), U1.10 (DGND), U1.17 (!CS)
unnamed: C1.2, Q1.1, U1.15 (CLKIN)
unnamed: C2.2, Q1.2, U1.16 (CLKOUT)
unnamed: R1.1, U1.1 (!RESET)
unnamed: C5.1, C6.1, R2.2, U1.3 (AVDD)
unnamed: C7.1, C8.1, U1.9 (REF)

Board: 2 copper layers, 20 parts (0 on the bottom side), 14 nets, no tracks yet.

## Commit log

2015-03-18 :lollipop: Added .gitattributes & .gitignore files
2015-03-23 init board
2015-03-25 add dht, mq6, and mq7 sensors
2015-03-25 rename edited files
2015-03-28 add grber, chg ems_mbed w/ corct ones, del oth file
2015-04-08 add ems_mbed_rev_b
2015-04-13 add eth_module
2015-05-25 add doc for SLA
2015-06-04 add mqtt and rest code for esp8266
    use "tuanpm" firmware
2015-06-15 add esp_mqtt_revA code using Tigor's thingfabric
2015-06-25 backup mbed code

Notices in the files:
parts and their libraries:
m-pad-2.1: License : GNU General Public License version 2 (see bottom)
SparkFun-Passives: Licensing: CC v3.0 Share-Alike You are welcome to use this library for commercial purposes.
microbuilder: Shamelessly taken from the Adafruit Eagle library (public domain) ... thanks!
